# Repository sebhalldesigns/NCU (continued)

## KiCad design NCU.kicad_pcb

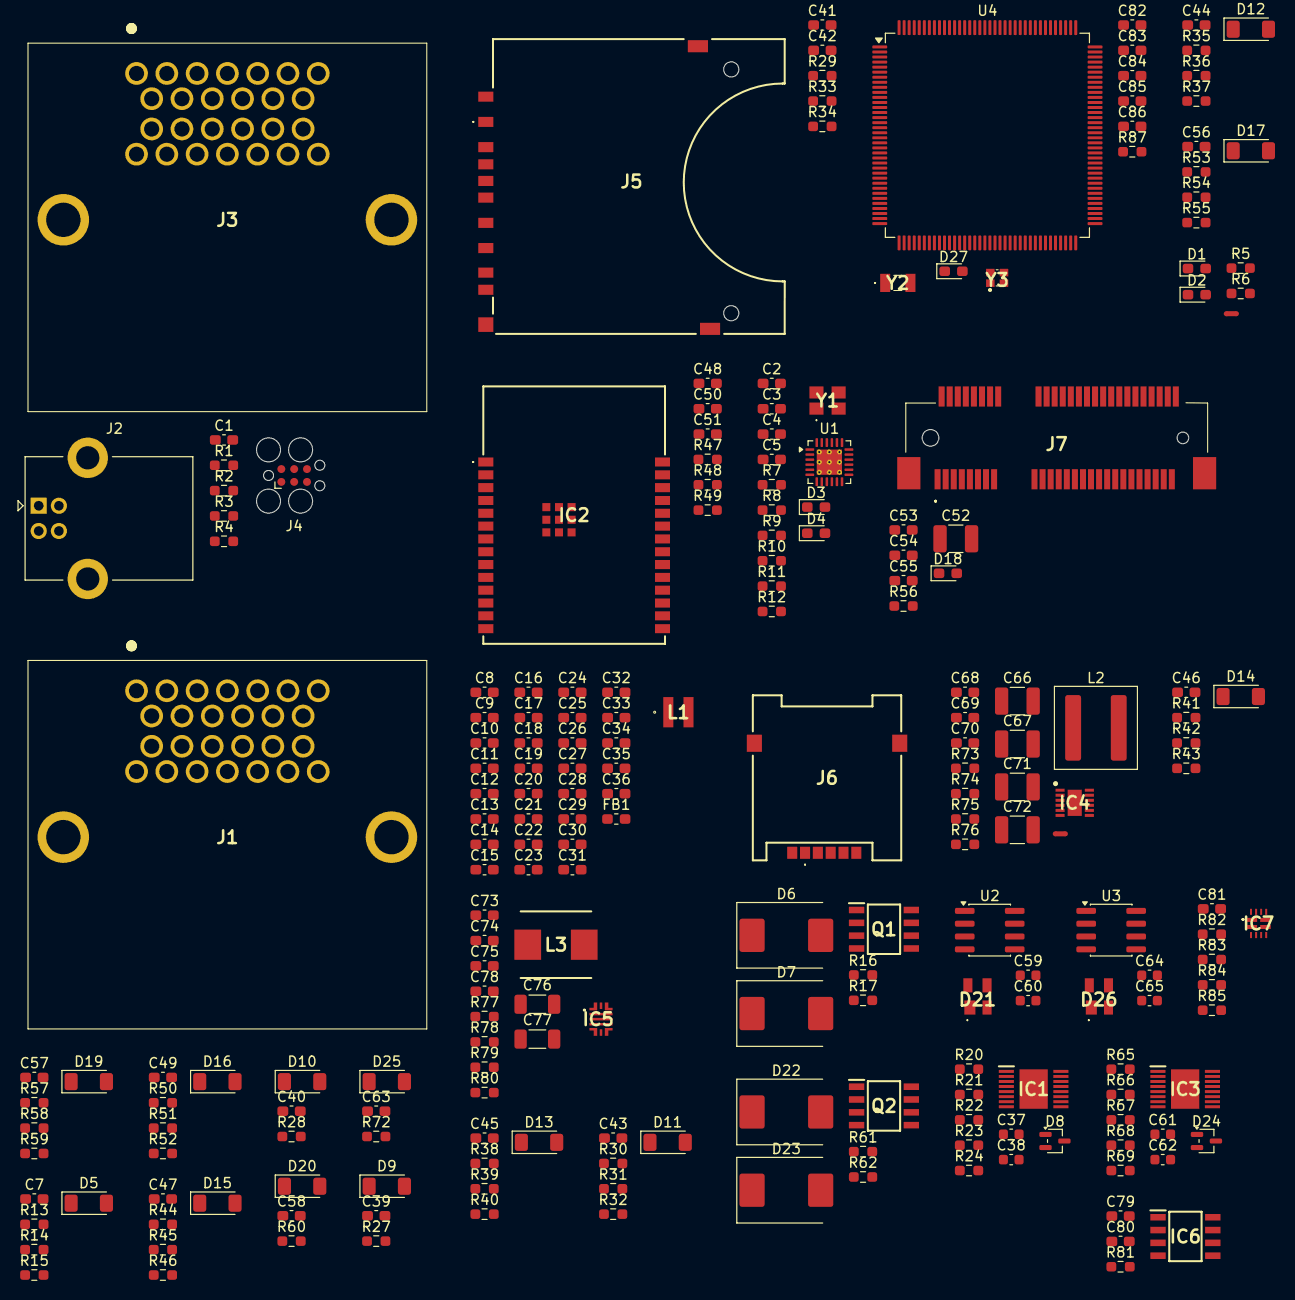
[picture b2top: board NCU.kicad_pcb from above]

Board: 2 copper layers, 219 parts (0 on the bottom side), 167 nets, no tracks yet.

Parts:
C1, C2, C4, C7, C9, C10, C11, C13, C14, C15, C16, C18, C20, C21, C22, C23, C24, C25, C26, C31, C33, C35, C36, C39, C40, C42, C43, C44, C45, C46, C47, C49, C54, C55, C56, C57, C58, C63, C82: 100nF; C_0603_1608Metric_Pad1.08x0.95mm_HandSolder
C3, C17, C19, C29, C41, C53: 10uF; C_0603_1608Metric_Pad1.08x0.95mm_HandSolder
C5, C75: 10pF; C_0603_1608Metric_Pad1.08x0.95mm_HandSolder
C8: 4.7uF; C_0603_1608Metric_Pad1.08x0.95mm_HandSolder
C12, C28, C34, C79, C80: 1uF; C_0603_1608Metric_Pad1.08x0.95mm_HandSolder
C27: 220pF; C_0603_1608Metric_Pad1.08x0.95mm_HandSolder
C30, C32: 2.2uF; C_0603_1608Metric_Pad1.08x0.95mm_HandSolder
C37, C61: 10u; C_0603_1608Metric
C38, C60, C62, C65: 100n; C_0603_1608Metric
C48, C81: 1u; C_0603_1608Metric_Pad1.08x0.95mm_HandSolder
C50: 10u; C_0603_1608Metric_Pad1.08x0.95mm_HandSolder
C51: 100n; C_0603_1608Metric_Pad1.08x0.95mm_HandSolder
C52: 100uF; C_1210_3225Metric_Pad1.33x2.70mm_HandSolder
C59, C64: 1u; C_0603_1608Metric
C66, C67: 4.7uF; C_1210_3225Metric_Pad1.33x2.70mm_HandSolder
C68, C69: 0.1uF; C_0603_1608Metric_Pad1.08x0.95mm_HandSolder
C70: 33pF; C_0603_1608Metric_Pad1.08x0.95mm_HandSolder
C71, C72: 47uF; C_1210_3225Metric_Pad1.33x2.70mm_HandSolder
C73: 4.7nF; C_0603_1608Metric_Pad1.08x0.95mm_HandSolder
C74, C78: 22uF; C_0603_1608Metric_Pad1.08x0.95mm_HandSolder
C76, C77: 22uF; L_1206_3216Metric_Pad1.22x1.90mm_HandSolder
C83, C85: 5.6pF; C_0603_1608Metric_Pad1.08x0.95mm_HandSolder
C84, C86: 5.1pF; C_0603_1608Metric_Pad1.08x0.95mm_HandSolder
D1, D2, D3, D4, D18, D27: LED; LED_0603_1608Metric_Pad1.05x0.95mm_HandSolder
D5, D9, D10, D11, D12, D13, D14, D15, D16, D17, D19, D20, D25: BZV55C3V6; D_MiniMELF
D6, D7, D22, D23: B340; D_SMC
D8, D24: BAT54W; SOT-323_SC-70
D21, D26: SP0503BAHTG
FB1: FCM 1608KF-471T03; L_0603_1608Metric_Pad1.05x0.95mm_HandSolder
IC1, IC3: VND7E025AJTR; SOP50P600X170-17N
IC2: ESP32-C6-WROOM-1-N8; ESP32C6WROOM1N8
IC4: LMR51460SQDRRRQ1; SON50P300X300X80-13N-D
IC5: TPS628101HQWRWYRQ1; TPS6281008QWRWYRQ1
IC6: LP2951-50DRG4; SOIC127P600X175-8N
IC7: TPS2121RUXT
J1, J3: 6437288-4; 64372884
J2: USB_B; USB_B_Lumberg_2411_02_Horizontal
J4: Conn_ARM_SWD_TagConnect_TC2030; Tag-Connect_TC2030-IDC-FP_2x03_P1.27mm_Vertical
J5: GSD09002SEU
J6: MSIM-11-C; MSIM11C
J7: 2041262-1; 20412621
L1: VLS3015CX-2R2M-H; VLS3015
L2: 4.7uH; L_Coilcraft_XAL7030-472
L3: 0.47uH; INDPM7066X240N
NT1, NT2: NetTie_2; NetTie-2_SMD_Pad0.5mm
Q1, Q2: STS5DNF60L; SOIC127P600X175-8N
R1, R2, R3, R4: 47R; R_0603_1608Metric_Pad0.98x0.95mm_HandSolder
R5: 2k; R_0603_1608Metric_Pad0.98x0.95mm_HandSolder
R6, R87: 260R; R_0603_1608Metric_Pad0.98x0.95mm_HandSolder
R7, R9, R56: 680R; R_0603_1608Metric_Pad0.98x0.95mm_HandSolder
R8, R29: 10R; R_0603_1608Metric_Pad0.98x0.95mm_HandSolder
R10: 12.4k; R_0603_1608Metric_Pad0.98x0.95mm_HandSolder
R11, R12, R33, R34, R42, R45, R48, R49, R51, R54, R58: 10k; R_0603_1608Metric_Pad0.98x0.95mm_HandSolder
R13, R27, R28, R30, R35, R38, R41, R44, R50, R53, R57, R60, R72: 100; R_0603_1608Metric_Pad0.98x0.95mm_HandSolder
R14, R31, R36, R39, R43, R46, R52, R55, R59, R76: 1k; R_0603_1608Metric_Pad0.98x0.95mm_HandSolder
R15, R32, R37, R40: 1.5k; R_0603_1608Metric_Pad0.98x0.95mm_HandSolder
R16, R17, R61, R62: 33R; R_0603_1608Metric_Pad0.98x0.95mm_HandSolder
R20, R21, R22, R23, R65, R66, R67, R68: 15k; R_0603_1608Metric_Pad0.98x0.95mm_HandSolder
R24, R69: 620R; R_0603_1608Metric_Pad0.98x0.95mm_HandSolder
R47, R74, R75, R77, R81: 100k; R_0603_1608Metric_Pad0.98x0.95mm_HandSolder
R73: 19.1k; R_0603_1608Metric_Pad0.98x0.95mm_HandSolder
R78: 8.06k; R_0603_1608Metric_Pad0.98x0.95mm_HandSolder
R79: 88.7k; R_0603_1608Metric_Pad0.98x0.95mm_HandSolder
R80: 19.6k; R_0603_1608Metric_Pad0.98x0.95mm_HandSolder
R82, R84: 18k; R_0603_1608Metric_Pad0.98x0.95mm_HandSolder
R83: 5k; R_0603_1608Metric_Pad0.98x0.95mm_HandSolder
R85: 22.1k; R_0603_1608Metric_Pad0.98x0.95mm_HandSolder
U1: LAN8742A; VQFN-24-1EP_4x4mm_P0.5mm_EP2.5x2.5mm_ThermalVias
U2, U3: SN65HVD230; SOIC-8_3.9x4.9mm_P1.27mm
U4: STM32H745ZITx; LQFP-144_20x20mm_P0.5mm
Y1: LFXTAL071758Cutt
Y2: NX3215SA-32.768K-STD-MUS-2; NX3215SA32768KSTDMUS2
Y3: Crystal_GND24; NX2016SA32MEXS00ACS06465

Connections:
3V3: C1.1, C4.1, C8.1, C9.1, C10.1, C11.1, C12.1, C13.1, C14.1, C15.1, C16.1, C17.1, C18.1, C19.1, C20.1, C21.1, C22.1, C23.1, C24.1, C25.1, C26.1, C50.1, C51.1, C52.1, C53.1, C54.1, C55.1, C59.1, C60.1, C64.1, C65.1, C75.1, C76.1, C77.1, C78.1, FB1.1, IC2.2 (3V3), J4.1 (VCC), J7.2, J7.39, J7.41, J7.52, L3.2, R6.1, R7.1, R8.1, R11.1, R12.1, R29.2, R33.1, R34.1, R47.1, R48.1, R49.1, R74.2, R77.2, R79.2, R81.2, R84.1, U1.6 (VDDCR), U1.9 (VDDIO), U2.3 (VCC), U3.3 (VCC), U4.7 (VDD), U4.8 (VBAT), U4.13 (VDD), U4.16 (VDDSMPS), U4.19 (VDD), U4.32 (VDD), U4.42 (VDD), U4.56 (VDD), U4.71 (VDD), U4.79 (VDD), U4.90 (VDD50_USB), U4.91 (VDD33_USB), U4.92 (VDD), U4.106 (VDD), U4.119 (VDD), U4.129 (VDD), U4.144 (VDD)
5V: C74.1, IC5.1 (MODE/SYNC_1), IC5.2 (VIN), IC5.8 (EN_1), IC5.10 (MODE/SYNC_2), IC5.13 (EN_2), IC7.1 (OUT_1), IC7.8 (OUT_2)
12V: C37.1, C38.1, C61.1, C62.1, C66.1, C67.1, C68.1, C79.1, D6.1 (K), D7.1 (K), D22.1 (K), D23.1 (K), IC1.17 (VCC), IC3.17 (VCC), IC4.9 (EN), IC4.10 (VIN_1), IC4.11 (VIN_2), IC4.12 (VIN_3), IC6.8 (INPUT), J1.3, J1.4, R5.1
/CARD_SD/SD_CD: J5.10 (CD), R33.2, U4.99 (PA10)
/CARD_SD/SD_CLK: J5.5 (MMC-CLK/SD-CLK), U4.111 (SDMMC1_CK)
/CARD_SD/SD_CMD: J5.2 (MMC-CMD/SD-CMD), U4.114 (SDMMC1_CMD)
/CARD_SD/SD_DAT0: J5.7 (MMC-DAT/SD-DAT0), U4.95 (SDMMC1_D0)
/CARD_SD/SD_DAT1: J5.8 (SD-DAT1), U4.96 (SDMMC1_D1)
/CARD_SD/SD_DAT2: J5.9 (SD-DAT2), U4.109 (SDMMC1_D2)
/CARD_SD/SD_DAT3: J5.1 (MMC-DAT/SD-DAT3), U4.110 (SDMMC1_D3)
/CARD_SD/SD_WP: J5.11 (WP), R34.2, U4.97 (PA8)
/CARD_SIM/USIM_CLK: J6.C3 (CLK), J7.12
/CARD_SIM/USIM_DATA: J6.C7 (I/O), J7.10
/CARD_SIM/USIM_RST: J6.C2 (RST), J7.14
/CARD_SIM/USIM_VDD: J6.C1 (VCC), J7.8
/CONN_A/CAN0_H: D26.3 (K_2), J1.6, U3.7 (CANH)
/CONN_A/CAN0_L: D26.4 (K_3), J1.5, U3.6 (CANL)
/CONN_A/CAN1_H: D21.3 (K_2), J1.8, U2.7 (CANH)
/CONN_A/CAN1_L: D21.4 (K_3), J1.7, U2.6 (CANL)
/CONN_A/HSD_0: IC3.13 (OUTPUT0_1), IC3.14 (OUTPUT0_2), IC3.15 (OUTPUT0_3), IC3.16 (OUTPUT0_4), J1.13
/CONN_A/HSD_1: IC3.9 (OUTPUT1_1), IC3.10 (OUTPUT1_2), IC3.11 (OUTPUT1_3), IC3.12 (OUTPUT1_4), J1.14
/CONN_A/HSD_2: IC1.13 (OUTPUT0_1), IC1.14 (OUTPUT0_2), IC1.15 (OUTPUT0_3), IC1.16 (OUTPUT0_4), J1.15
/CONN_A/HSD_3: IC1.9 (OUTPUT1_1), IC1.10 (OUTPUT1_2), IC1.11 (OUTPUT1_3), IC1.12 (OUTPUT1_4), J1.16
/CONN_A/LSD_0: D22.2 (A), J1.9, Q2.7 (D1_1), Q2.8 (D1_2)
/CONN_A/LSD_1: D23.2 (A), J1.10, Q2.5 (D2_1), Q2.6 (D2_2)
/CONN_A/LSD_2: D6.2 (A), J1.11, Q1.7 (D1_1), Q1.8 (D1_2)
/CONN_A/LSD_3: D7.2 (A), J1.12, Q1.5 (D2_1), Q1.6 (D2_2)
/CONN_B/ESP_BOOT: IC2.15 (IO9), J3.26, R47.2
/CONN_B/ESP_EN: C48.1, IC2.3 (EN), J3.25, R48.2
/CONN_B/ESP_RX: IC2.24 (RXD0), J3.24
/CONN_B/ESP_TX: IC2.25 (TXD0), J3.23
/CONN_B/ETH_RXM: J3.10, U1.22 (RXN)
/CONN_B/ETH_RXP: J3.9, U1.23 (RXP)
/CONN_B/ETH_TXM: J3.8, U1.20 (TXN)
/CONN_B/ETH_TXP: J3.7, U1.21 (TXP)
/CONN_B/GPIO_0: J3.12, R72.1
/CONN_B/GPIO_1: J3.13, R27.1
/CONN_B/GPIO_2: J3.14, R28.1
/CONN_B/GPIO_3: J3.15, R60.1
/CONN_B/PCIE_RST: J3.22, J7.22
/CONN_B/PCIE_USB_DM: J3.6, J7.36
/CONN_B/PCIE_USB_DP: J3.5, J7.38
/CONN_B/STM_NRST: C82.1, R4.1, U4.27 (NRST)
/CONN_B/STM_SWDCLK: R2.1, U4.107 (DEBUG_JTCK-SWCLK)
/CONN_B/STM_SWDIO: R1.1, U4.102 (DEBUG_JTMS-SWDIO)
/CONN_B/STM_SWO: R3.1, U4.130 (DEBUG_JTDO-SWO)
/CONN_B/STM_USB_DM: J2.2 (D-), J3.4, U4.100 (USB_OTG_FS_DM)
/CONN_B/STM_USB_DP: J2.3 (D+), J3.3, U4.101 (USB_OTG_FS_DP)
/DRIVES/HSD0_CTRL: R65.1, U4.82 (TIM4_CH1)
/DRIVES/HSD1_CTRL: R68.1, U4.83 (TIM4_CH2)
/DRIVES/HSD01_EN: R66.1, U4.81 (PD11)
/DRIVES/HSD01_ISEN: IC3.7 (CS), R69.2, U4.20 (ADC3_INP8)
/DRIVES/HSD01_SEL: R67.1, U4.21 (PF7)
/DRIVES/HSD2_CTRL: R20.1, U4.136 (TIM4_CH3)
/DRIVES/HSD3_CTRL: R23.1, U4.137 (TIM4_CH4)
/DRIVES/HSD23_EN: R21.1, U4.134 (PB7)
/DRIVES/HSD23_ISEN: IC1.7 (CS), R24.2, U4.22 (ADC3_INP7)
/DRIVES/HSD23_SEL: R22.1, U4.23 (PF9)
/DRIVES/LSD0_CTRL: R61.1, U4.59 (TIM1_CH1)
/DRIVES/LSD1_CTRL: R62.1, U4.61 (TIM1_CH2)
/DRIVES/LSD2_CTRL: R16.1, U4.63 (TIM1_CH3)
/DRIVES/LSD3_CTRL: R17.1, U4.64 (TIM1_CH4)
/GPIO/GPIO0_IO: C63.1, D25.1 (K), R72.2, U4.43 (DAC1_OUT1)
/GPIO/GPIO1_IO: C39.1, D9.1 (K), R27.2, U4.44 (DAC1_OUT2)
/GPIO/GPIO2_IO: C40.1, D10.1 (K), R28.2, U4.37 (ADC1_INP16)
/GPIO/GPIO3_IO: C58.1, D20.1 (K), R60.2, U4.38 (ADC1_INP17)
/INPUTS/INPUT_5V_0/IO: C44.1, D12.1 (K), R36.2, R37.1
/INPUTS/INPUT_5V_1/IO: C7.1, D5.1 (K), R14.2, R15.1
/INPUTS/INPUT_5V_2/IO: C43.1, D11.1 (K), R31.2, R32.1
/INPUTS/INPUT_5V_3/IO: C45.1, D13.1 (K), R39.2, R40.1
/INPUTS/INPUT_20V_0/IO: C49.1, D16.1 (K), R51.2, R52.1
/INPUTS/INPUT_20V_1/IO: C46.1, D14.1 (K), R42.2, R43.1
/INPUTS/INPUT_20V_2/IO: C47.1, D15.1 (K), R45.2, R46.1
/INPUTS/INPUT_20V_3/IO: C56.1, D17.1 (K), R54.2, R55.1
/INPUTS/INPUT_20V_12V/IO: C57.1, D19.1 (K), R58.2, R59.1
/MCU/3V3_PG: IC5.9 (PG), R77.1, U4.116 (PD4)
/MCU/A5V_PG: IC6.5 (~ERROR), R81.1, U4.117 (PD5)
/MCU/CAN0_RX: U3.4 (R), U4.112 (FDCAN1_RX)
/MCU/CAN0_TX: U3.1 (D), U4.113 (FDCAN1_TX)
/MCU/CAN1_RX: U2.4 (R), U4.132 (FDCAN2_RX)
/MCU/CAN1_TX: U2.1 (D), U4.133 (FDCAN2_TX)
/MCU/ESP_SPI_CLK: IC2.6 (IO6), U4.1 (SPI4_SCK)
/MCU/ESP_SPI_CS: IC2.16 (IO18), U4.3 (SPI4_NSS)
/MCU/ESP_SPI_MISO: IC2.27 (IO2), U4.4 (SPI4_MISO)
/MCU/ESP_SPI_MOSI: IC2.7 (IO7), U4.5 (SPI4_MOSI)
/MCU/ETH_CRS_DV: U1.11 (CRS_DV/MODE2), U4.46 (ETH_CRS_DV)
/MCU/ETH_INT: R12.2, U1.14 (~INT/REFCLKO), U4.49 (PB0)
/MCU/ETH_MDC: U1.13 (MDC), U4.29 (ETH_MDC)
/MCU/ETH_MDIO: U1.12 (MDIO), U4.39 (ETH_MDIO)
/MCU/ETH_RST: R11.2, U1.15 (~RST), U4.108 (PA15)
/MCU/ETH_RXD0: U1.8 (RXD0/MODE0), U4.47 (ETH_RXD0)
/MCU/ETH_RXD1: U1.7 (RXD1/MODE1), U4.48 (ETH_RXD1)
/MCU/ETH_TXD0: U1.17 (TXD0), U4.72 (ETH_TXD0)
/MCU/ETH_TXD1: U1.18 (TXD1), U4.73 (ETH_TXD1)
/MCU/ETH_TXEN: U1.16 (TXEN), U4.67 (ETH_TX_EN)
/MCU/LV_PG: IC4.5 (PG), R74.1, U4.115 (PD3)
/MCU/MCU Power/1V2_MCU: C29.1, C33.1, C35.1, L1.2, U4.70 (VDDLDO), U4.105 (VDDLDO), U4.143 (VDDLDO)
/MCU/PCIE_UART_CTS: J7.23, U4.84 (UART8_CTS)
/MCU/PCIE_UART_RTS: J7.25, U4.85 (UART8_RTS)
/MCU/PCIE_W_DISABLE: IC7.9 (ST), J7.20, R84.2, U4.120 (PD6)
/MCU/RCC_OSC_IN: C85.1, C86.1, U4.25 (RCC_OSC_IN), Y2.2, Y3.1
/MCU/RCC_OSC_OUT: C83.1, C84.1, U4.26 (RCC_OSC_OUT), Y2.1, Y3.3
/MCU/VCAP: C30.1, C32.1, U4.17 (VFBSMPS), U4.68 (VCAP), U4.103 (VCAP), U4.140 (VCAP)
/MCU/VLXSMPS: C27.1, L1.1, U4.15 (VLXSMPS)
/MCU/VREF+: C28.1, C31.1, C34.1, C36.1, FB1.2, U4.35 (VREF+), U4.36 (VDDA)
/MOD_PCIE/UART_RX: J3.20, J7.11, U4.139 (UART8_TX)
/MOD_PCIE/UART_TX: J3.21, J7.13, U4.138 (UART8_RX)
/PWR/PWR_3V3/TPS_CF: IC5.7 (COMP/_FSET_1), IC5.12 (COMP/_FSET_2), R78.2
/PWR/PWR_3V3/TPS_FB: C75.2, IC5.5 (FB_1), IC5.11 (FB_2), R79.1, R80.2
/PWR/PWR_LV_5V/LMR_FB: C70.2, IC4.7 (FB), R73.1, R75.2
A5V: C80.1, IC6.1 (OUTPUT), IC6.2 (SENSE), J1.25
AGND: C7.2, C28.2, C31.2, C34.2, C36.2, C43.2, C44.2, C45.2, C80.2, D5.2 (A), D11.2 (A), D12.2 (A), D13.2 (A), IC6.3 (SHUTDOWN), IC6.4 (GND), J1.26, NT1.2, R15.2, R32.2, R37.2, R40.2, U4.34 (VSSA)
GND: C1.2, C2.2, C3.2, C4.2, C5.2, C8.2, C9.2, C10.2, C11.2, C12.2, C13.2, C14.2, C15.2, C16.2, C17.2, C18.2, C19.2, C20.2, C21.2, C22.2, C23.2, C24.2, C25.2, C26.2, C27.2, C29.2, C30.2, C32.2, C33.2, C35.2, C37.2, C38.2, C39.2, C40.2, C41.2, C42.2, C46.2, C47.2, C48.2, C49.2, C50.2, C51.2, C52.2, C53.2, C54.2, C55.2, C56.2, C57.2, C58.2, C59.2, C60.2, C61.2, C62.2, C63.2, C64.2, C65.2, C66.2, C67.2, C68.2, C71.2, C72.2, C73.2, C74.2, C76.2, C77.2, C78.2, C79.2, C81.2, C82.2, C83.2, C84.2, C85.2, C86.2, D1.1 (K), D2.1 (K), D4.1 (K), D8.1 (A), D9.2 (A), D10.2 (A), D14.2 (A), D15.2 (A), D16.2 (A), D17.2 (A), D19.2 (A), D20.2 (A), D21.1 (COMMON_A), D24.1 (A), D25.2 (A), D26.1 (COMMON_A), D27.1 (K), IC2.1 (GND_1), IC2.28 (GND_2), IC2.29 (GND_3), IC2.30 (GND_4), IC2.31 (GND_5), IC2.32 (GND_6), IC2.33 (GND_7), IC2.34 (GND_8), IC2.35 (GND_9), IC2.36 (GND_10), IC2.37 (GND_11), IC4.13 (PGND/DAP), IC5.4 (GND), IC7.3 (CP2), IC7.4 (OV2), IC7.5 (OV1), IC7.12 (GND), J1.1, J1.2, J1.MH1, J1.MH2, J2.4 (GND), J2.5 (Shield), J3.1, J3.MH1, J3.MH2, J4.5 (GND), J5.3 (MMC-VSS1/SD-VSS1), J5.6 (MMC-VSS2/SD-VSS2), J5.12 (GROUND_1), J5.13 (GROUND_2), J6.C5 (GND), J6.MP1, J6.MP2, J7.4, J7.9, J7.15, J7.18, J7.21, J7.26, J7.27, J7.29, J7.34, J7.35, J7.37, J7.40, J7.43, J7.50, J7.MP1, J7.MP2, NT1.1, NT2.1, Q1.1 (S1), Q1.3 (S2), Q2.1 (S1), Q2.3 (S2), R10.1, R24.1, R43.2, R46.2, R52.2, R55.2, R59.2, R69.1, R78.1, R80.1, R83.2, R85.2, U1.10 (RXER/PHYAD0), U1.25 (VSS), U2.2 (GND), U2.8 (Rs), U3.2 (GND), U3.8 (Rs), U4.6 (VSS), U4.12 (VSS), U4.14 (VSSSMPS), U4.18 (VSS), U4.33 (VSS), U4.41 (VSS), U4.55 (VSS), U4.69 (VSS), U4.80 (VSS), U4.89 (VSS), U4.104 (VSS), U4.118 (VSS), U4.128 (VSS), U4.141 (VSS), Y1.2 (GND_1), Y1.4 (GND_2), Y3.2, Y3.4
LV_5V: C71.1, C72.1, IC7.7 (IN1), L2.2, R75.1, R76.1, R82.1
unnamed: C70.1, R76.2
unnamed: D1.2 (A), R5.2
unnamed: D2.2 (A), R6.2
unnamed: D3.2 (A), U1.2 (LED2/~INTSEL)
unnamed: D3.1 (K), R7.2
unnamed: D4.2 (A), R9.2
unnamed: D8.3 (K), IC1.4 (GND)
unnamed: D18.2 (A), J7.42
unnamed: D18.1 (K), R56.2
unnamed: D24.3 (K), IC3.4 (GND)
unnamed: D27.2 (A), R87.2
unnamed: IC1.1 (INPUT0), R20.2
unnamed: IC1.8 (INPUT1), R23.2
unnamed: IC1.5 (SEL0), R22.2
unnamed: IC1.3 (SEN), R21.2
unnamed: IC2.10 (IO8), R49.2
unnamed: IC3.1 (INPUT0), R65.2
unnamed: IC3.8 (INPUT1), R68.2
unnamed: IC3.5 (SEL0), R67.2
unnamed: IC3.3 (SEN), R66.2
unnamed: IC4.8 (AGND), NT2.2, R73.2
unnamed: C69.2, IC4.4 (BOOT)
unnamed: C69.1, IC4.1 (SW_1), IC4.2 (SW_2), IC4.3 (SW_3), L2.1
unnamed: C73.1, IC5.6 (SS/TR)
unnamed: IC5.3 (SW), L3.1
unnamed: IC6.6 (VTAP), IC6.7 (FEEDBACK)
unnamed: IC7.10 (ILIM), R85.1
unnamed: IC7.6 (PR1), R82.2, R83.1
unnamed: C81.1, IC7.11 (SS)
unnamed: J3.17, J4.4 (SWCLK), R2.2
unnamed: J3.16, J4.2 (SWDIO), R1.2
unnamed: J3.18, J4.6 (SWO), R3.2
unnamed: J3.19, J4.3 (~RESET), R4.2
unnamed: C41.1, C42.1, J5.4 (MMC-VDD/SD-VDD), R29.1
unnamed: Q1.2 (G1), R16.2
unnamed: Q1.4 (G2), R17.2
unnamed: Q2.2 (G1), R61.2
unnamed: Q2.4 (G2), R62.2
unnamed: R13.2, R14.1
unnamed: R30.2, R31.1
unnamed: R35.2, R36.1
unnamed: R38.2, R39.1
unnamed: R41.2, R42.1
unnamed: R44.2, R45.1
unnamed: R50.2, R51.1
unnamed: R53.2, R54.1
unnamed: R57.2, R58.1
unnamed: R9.1, U1.3 (LED1/REGOFF)
unnamed: R10.2, U1.24 (RBIAS)
unnamed: C2.1, C3.1, R8.2, U1.1 (VDD2A), U1.19 (VDD1A)
unnamed: C5.1, U1.5 (XTAL1/CLKIN), Y1.1 (CRYSTAL_1)
unnamed: U1.4 (XTAL2), Y1.3 (CRYSTAL_2)
USB_VBUS: IC7.2 (IN2), J2.1 (VBUS), J3.2, U4.98 (USB_OTG_FS_VBUS)

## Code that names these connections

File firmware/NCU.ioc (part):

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Mcu.Name=STM32H745ZITx
Mcu.Package=LQFP144
Mcu.UserName=STM32H745ZITx
PA0.Signal=ADC1_INP16
PA1.Signal=ADC1_INP17
PA11.Signal=USB_OTG_FS_DM
PA12.Signal=USB_OTG_FS_DP
PA13\ (JTMS/SWDIO).Signal=DEBUG_JTMS-SWDIO
PA14\ (JTCK/SWCLK).Signal=DEBUG_JTCK-SWCLK
PA2.Signal=ETH_MDIO
PA3.Signal=ADCx_INP15
PA4.Signal=COMP_DAC11_group
PA5.Signal=COMP_DAC12_group
PA6.Signal=ADCx_INP3
PA7.Signal=ETH_CRS_DV
PA9.Signal=USB_OTG_FS_VBUS
PB1.Signal=ADCx_INP5
PB11.Signal=ETH_TX_EN
PB12.Signal=ETH_TXD0
PB13.Signal=ETH_TXD1
PB3\ (JTDO/TRACESWO).Signal=DEBUG_JTDO-SWO
PB5.GPIOParameters=PinAttribute
PB5.PinAttribute=CortexM7
PB5.Signal=FDCAN2_RX
PB6.GPIOParameters=PinAttribute
PB6.PinAttribute=CortexM7
PB6.Signal=FDCAN2_TX
PB8.Signal=S_TIM4_CH3
PB9.Signal=S_TIM4_CH4
PC0.Signal=ADCx_INP10
PC1.Signal=ETH_MDC
PC10.Signal=SDMMC1_D2
PC11.Signal=SDMMC1_D3
PC12.Signal=SDMMC1_CK
PC14-OSC32_IN\ (OSC32_IN).GPIOParameters=PinAttribute
PC14-OSC32_IN\ (OSC32_IN).Mode=LSE-External-Oscillator
PC14-OSC32_IN\ (OSC32_IN).PinAttribute=Free
PC14-OSC32_IN\ (OSC32_IN).Signal=RCC_OSC32_IN
PC15-OSC32_OUT\ (OSC32_OUT).GPIOParameters=PinAttribute
PC15-OSC32_OUT\ (OSC32_OUT).Mode=LSE-External-Oscillator
PC15-OSC32_OUT\ (OSC32_OUT).PinAttribute=Free
PC15-OSC32_OUT\ (OSC32_OUT).Signal=RCC_OSC32_OUT
PC2_C.Signal=ADC3_INP0
PC3_C.Signal=ADC3_INP1
PC4.Signal=ETH_RXD0
PC5.Signal=ETH_RXD1
PC8.Signal=SDMMC1_D0
PC9.Signal=SDMMC1_D1
PD0.GPIOParameters=PinAttribute
PD0.PinAttribute=CortexM4
PD0.Signal=FDCAN1_RX
PD1.Signal=FDCAN1_TX
PD12.Signal=S_TIM4_CH1
PD13.Signal=S_TIM4_CH2
PD14.Signal=UART8_CTS
PD15.Signal=UART8_RTS
PD2.Signal=SDMMC1_CMD
PE0.Signal=UART8_RX
PE1.Signal=UART8_TX
PE11.Signal=S_TIM1_CH2
PE13.Signal=S_TIM1_CH3
PE14.Signal=S_TIM1_CH4
PE2.Signal=SPI4_SCK
PE4.Signal=SPI4_NSS
PE5.Signal=SPI4_MISO
PE6.Signal=SPI4_MOSI
PE9.Signal=S_TIM1_CH1
PF10.Signal=ADC3_INN2
PF11.Signal=ADC1_INP2
PF14.Signal=ADC2_INP6
PF6.Signal=SPI5_NSS
PF7.Signal=SPI5_SCK
PF8.Signal=SPI5_MISO
PF9.Signal=SPI5_MOSI
PH0-OSC_IN\ (PH0).GPIOParameters=PinAttribute
PH0-OSC_IN\ (PH0).Mode=HSE-External-Oscillator
PH0-OSC_IN\ (PH0).PinAttribute=Free
PH0-OSC_IN\ (PH0).Signal=RCC_OSC_IN
PH1-OSC_OUT\ (PH1).GPIOParameters=PinAttribute
PH1-OSC_OUT\ (PH1).Mode=HSE-External-Oscillator
PH1-OSC_OUT\ (PH1).PinAttribute=Free
PH1-OSC_OUT\ (PH1).Signal=RCC_OSC_OUT
RCC.SYSCLKFreq_VALUE=64000000
board=custom

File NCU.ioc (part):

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Mcu.Name=STM32H745ZITx
Mcu.Package=LQFP144
Mcu.UserName=STM32H745ZITx
PA0.Signal=ADC1_INP16
PA1.Signal=ADC1_INP17
PA11.Signal=USB_OTG_FS_DM
PA12.Signal=USB_OTG_FS_DP
PA13\ (JTMS/SWDIO).Signal=DEBUG_JTMS-SWDIO
PA14\ (JTCK/SWCLK).Signal=DEBUG_JTCK-SWCLK
PA15\ (JTDI).Signal=UART4_RTS
PA2.Signal=ETH_MDIO
PA3.Signal=ADCx_INP15
PA4.Signal=COMP_DAC11_group
PA5.Signal=COMP_DAC12_group
PA6.Signal=ADCx_INP3
PA7.Signal=ETH_CRS_DV
PA9.Signal=USB_OTG_FS_VBUS
PB0.Signal=UART4_CTS
PB1.Signal=ADCx_INP5
PB11.Signal=ETH_TX_EN
PB12.Signal=ETH_TXD0
PB13.Signal=ETH_TXD1
PB3\ (JTDO/TRACESWO).Signal=DEBUG_JTDO-SWO
PB5.GPIOParameters=PinAttribute
PB5.PinAttribute=CortexM7
PB5.Signal=FDCAN2_RX
PB6.GPIOParameters=PinAttribute
PB6.PinAttribute=CortexM7
PB6.Signal=FDCAN2_TX
PC0.Signal=ADCx_INP10
PC1.Signal=ETH_MDC
PC10.Signal=SDMMC1_D2
PC11.Signal=SDMMC1_D3
PC12.Signal=SDMMC1_CK
PC2_C.Signal=ADC3_INP0
PC3_C.Signal=ADC3_INP1
PC4.Signal=ETH_RXD0
PC5.Signal=ETH_RXD1
PC8.Signal=SDMMC1_D0
PC9.Signal=SDMMC1_D1
PD0.GPIOParameters=PinAttribute
PD0.PinAttribute=CortexM4
PD0.Signal=FDCAN1_RX
PD14.Signal=UART8_CTS
PD15.Signal=UART8_RTS
PD2.Signal=SDMMC1_CMD
PE0.Signal=UART8_RX
PE1.Signal=UART8_TX
PF10.Signal=ADC3_INN2
PF11.Signal=ADC1_INP2
PF14.Signal=ADC2_INP6
PF6.Signal=SPI5_NSS
PF7.Signal=SPI5_SCK
PF8.Signal=SPI5_MISO
PF9.Signal=SPI5_MOSI
RCC.SYSCLKFreq_VALUE=64000000
board=custom

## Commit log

2026-02-11 added initial components
2026-02-11 added ethernet chip
2026-02-15 work in progress
2026-02-23 worked on MII pinout
2026-02-23 updated to use RMII and routed ethernet and CAN from micro
2026-02-25 full initial power scheme
2026-02-25 improved power supplies, added ADCs
2026-03-02 added lib to project and added molex superseal connector
2026-03-04 added connects schematic, which is looking quite good
2026-03-04 routed more sheets, improved analogs. next 5v /analog ground
2026-03-05 improved analogs
2026-03-05 lsd circuit in place
2026-03-05 routed drives
2026-03-05 added 3.3v gpio input protection
2026-03-05 updated CAN
2026-03-05 possible working power mux
2026-03-05 power mux
2026-03-05 updated power layout
2026-03-06 added esp32
2026-03-06 finished initial esp routing
2026-03-06 added mini pcie connector
2026-03-06 added dip switches to wireless disables
2026-03-06 added inductor
2026-03-06 working on mcu layout
2026-03-06 added oscillators
2026-03-06 initial full port selection
2026-03-08 redid annotations, added test point
2026-03-08 moved pcb
2026-03-08 added generated cubemx code
2026-03-11 added better lsds
2026-03-11 power done
2026-03-11 CAN updated
2026-03-11 added USB protection, reviewed LSD and HSD, improved input TVS footprint
2026-03-11 updated ethernet
2026-03-11 updated wlan
2026-03-11 updated pcie sd and sim cards
2026-03-11 reannotated, updated some symbols
2026-03-12 minor changes before layout
2026-03-12 initial layout of pcb with connectors, wlan and pcie modules
2026-03-12 12v input layout done I think
2026-03-12 initial power mux layout
2026-03-12 improved current paths for power supplies
2026-03-12 all power supplies laid out I think
2026-03-12 initial microcontroller layout
2026-03-12 laid out analogs
2026-03-12 v2 analogs routing
2026-03-12 routed LSDs
2026-03-13 initial hsd layout
2026-03-13 improved power supplies I think
2026-03-13 improved power input stage, possible drive placement
2026-03-13 better power mux layout
2026-03-13 better placement of analogs incl. analog ldo
2026-03-13 routed hsds and lsds
2026-03-13 routed drives and analogs from conn a
2026-03-13 routing and power for analogs and hsds
2026-03-13 first pass of ethernet phy
2026-03-13 swapped sd to micro sd
2026-03-13 updated layout and locked micro location
2026-03-13 laid out most of esp
2026-03-13 started routing ethernet and other full length traces
2026-03-13 sd card slot initial attempt
2026-03-13 sd card slot initial attempt (I meant SIM before)
2026-03-14 initial routing of power for pcie, swapped switches for jumpers
2026-03-14 rerouted usb and comms signals
2026-03-14 spread out power and drives more
2026-03-14 full routing of LSD and HSD including control signals
2026-03-14 updated power nets
2026-03-14 improved analogs layout
2026-03-14 routed all traces from superseal connectors down
2026-03-14 routed 3v3 gpios
2026-03-14 routed can to transceivers
2026-03-14 fully routed CANs
2026-03-14 routed LSDs to micro
2026-03-14 pcie routing complete (except for status LED)
2026-03-14 started routing down SD lines
2026-03-14 removed solder jumpers for mcu power scheme, as taking up too much space on the board
2026-03-14 routed sd card
2026-03-14 routed swd, stm ethernet and esp en/boot
2026-03-14 initial ethernet routing
2026-03-14 routed analogs & gpios
2026-03-14 routed esp spi
2026-03-14 routed HSDs
2026-03-14 initial layout complete
2026-03-16 code restructure
2026-03-18 changed swd connector, removed ground trace between eth and usb lines
2026-03-18 removed AGND and added ground garden
2026-03-18 changed conn a pinout
2026-03-18 added back in jumpers for internal mcu power
2026-03-18 updated copper pour thermal reliefs
2026-03-18 added some thermal stiches, no DRC errors
2026-03-18 initial drc warnings complete
2026-03-18 updated design with tweaks to silkscreen and more pours on back copper
2026-03-19 added 10k resistor to USB VBUS line
2026-03-19 added jumper for VCAP connection to 1V2MCU. Fixed resistors on ethernet IF
2026-03-19 added jumper to external PCIE reset line. removed arrayed component ids and replaced with instance labels
2026-03-19 updated 3D bodies and gerbers
2026-03-19 as submitted to JLC
2026-04-01 updates from bom release
2026-04-17 updated to match board changes
